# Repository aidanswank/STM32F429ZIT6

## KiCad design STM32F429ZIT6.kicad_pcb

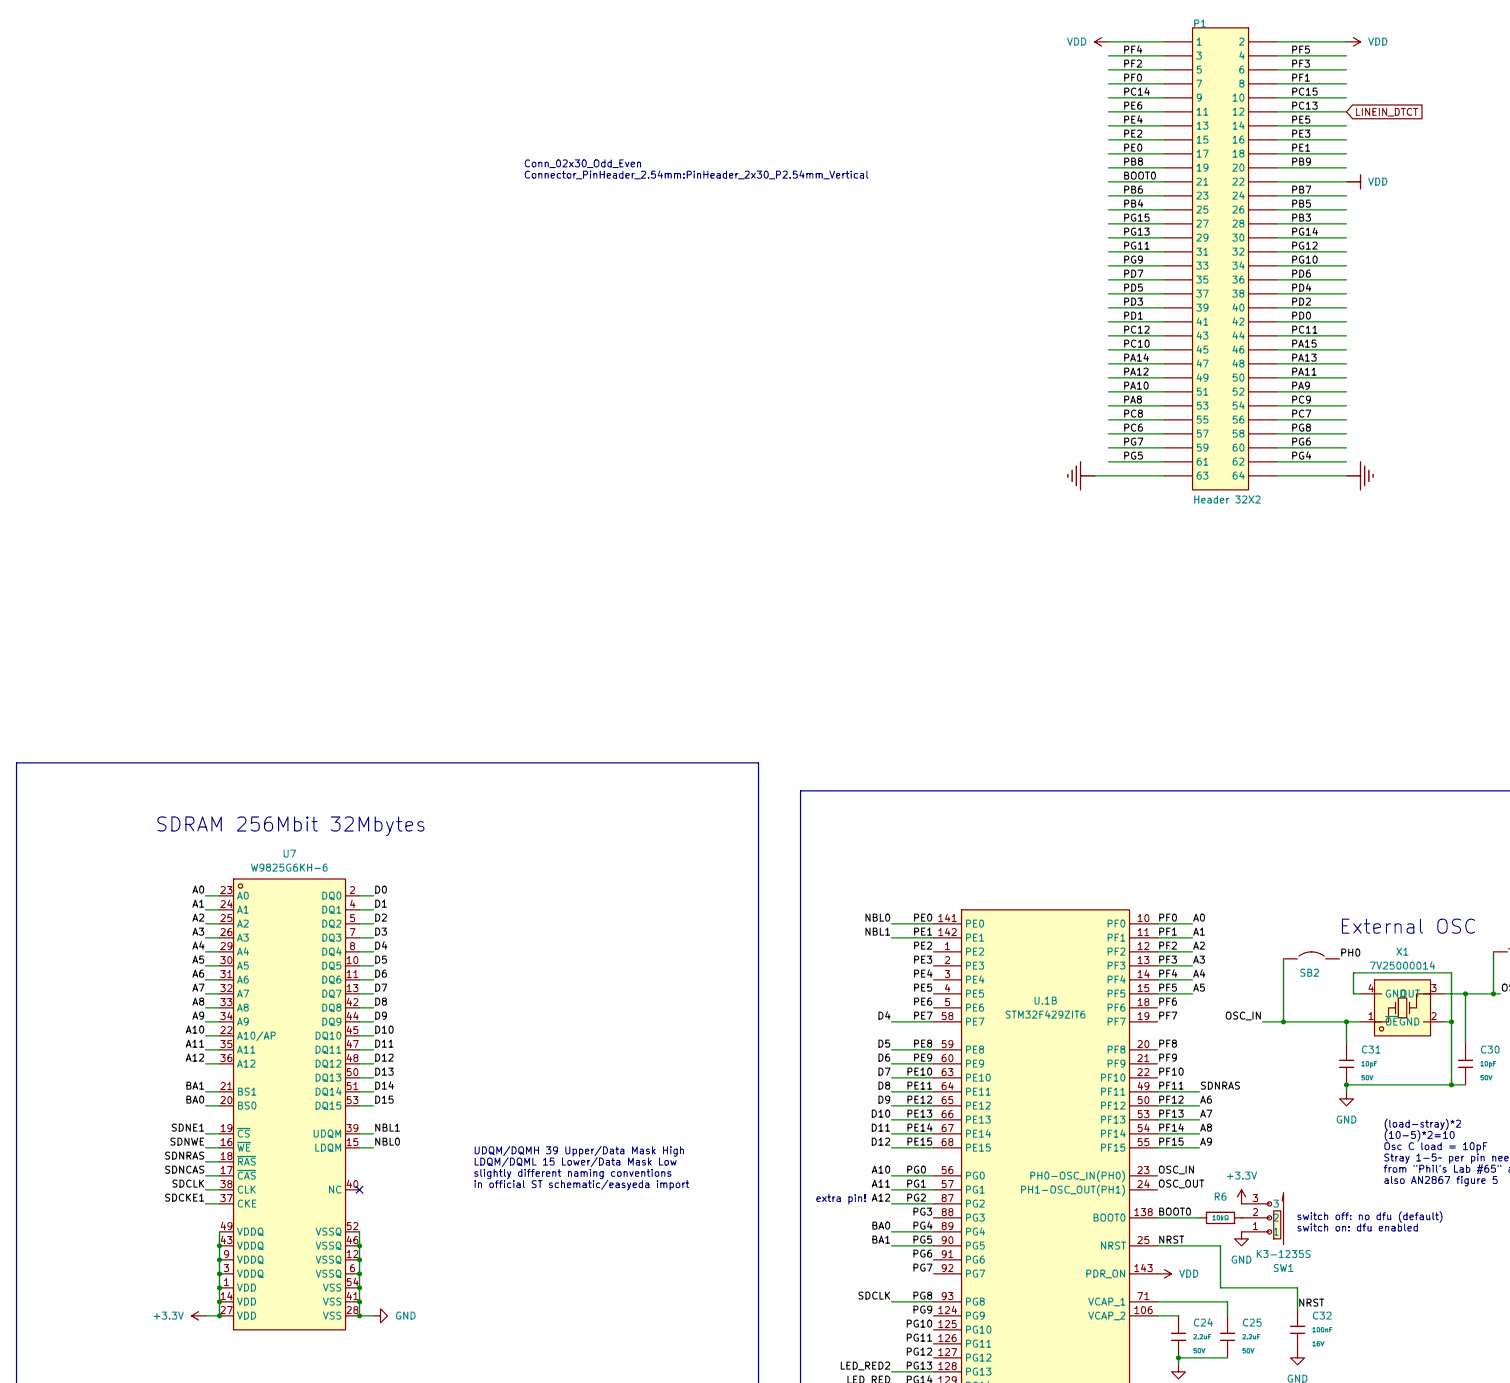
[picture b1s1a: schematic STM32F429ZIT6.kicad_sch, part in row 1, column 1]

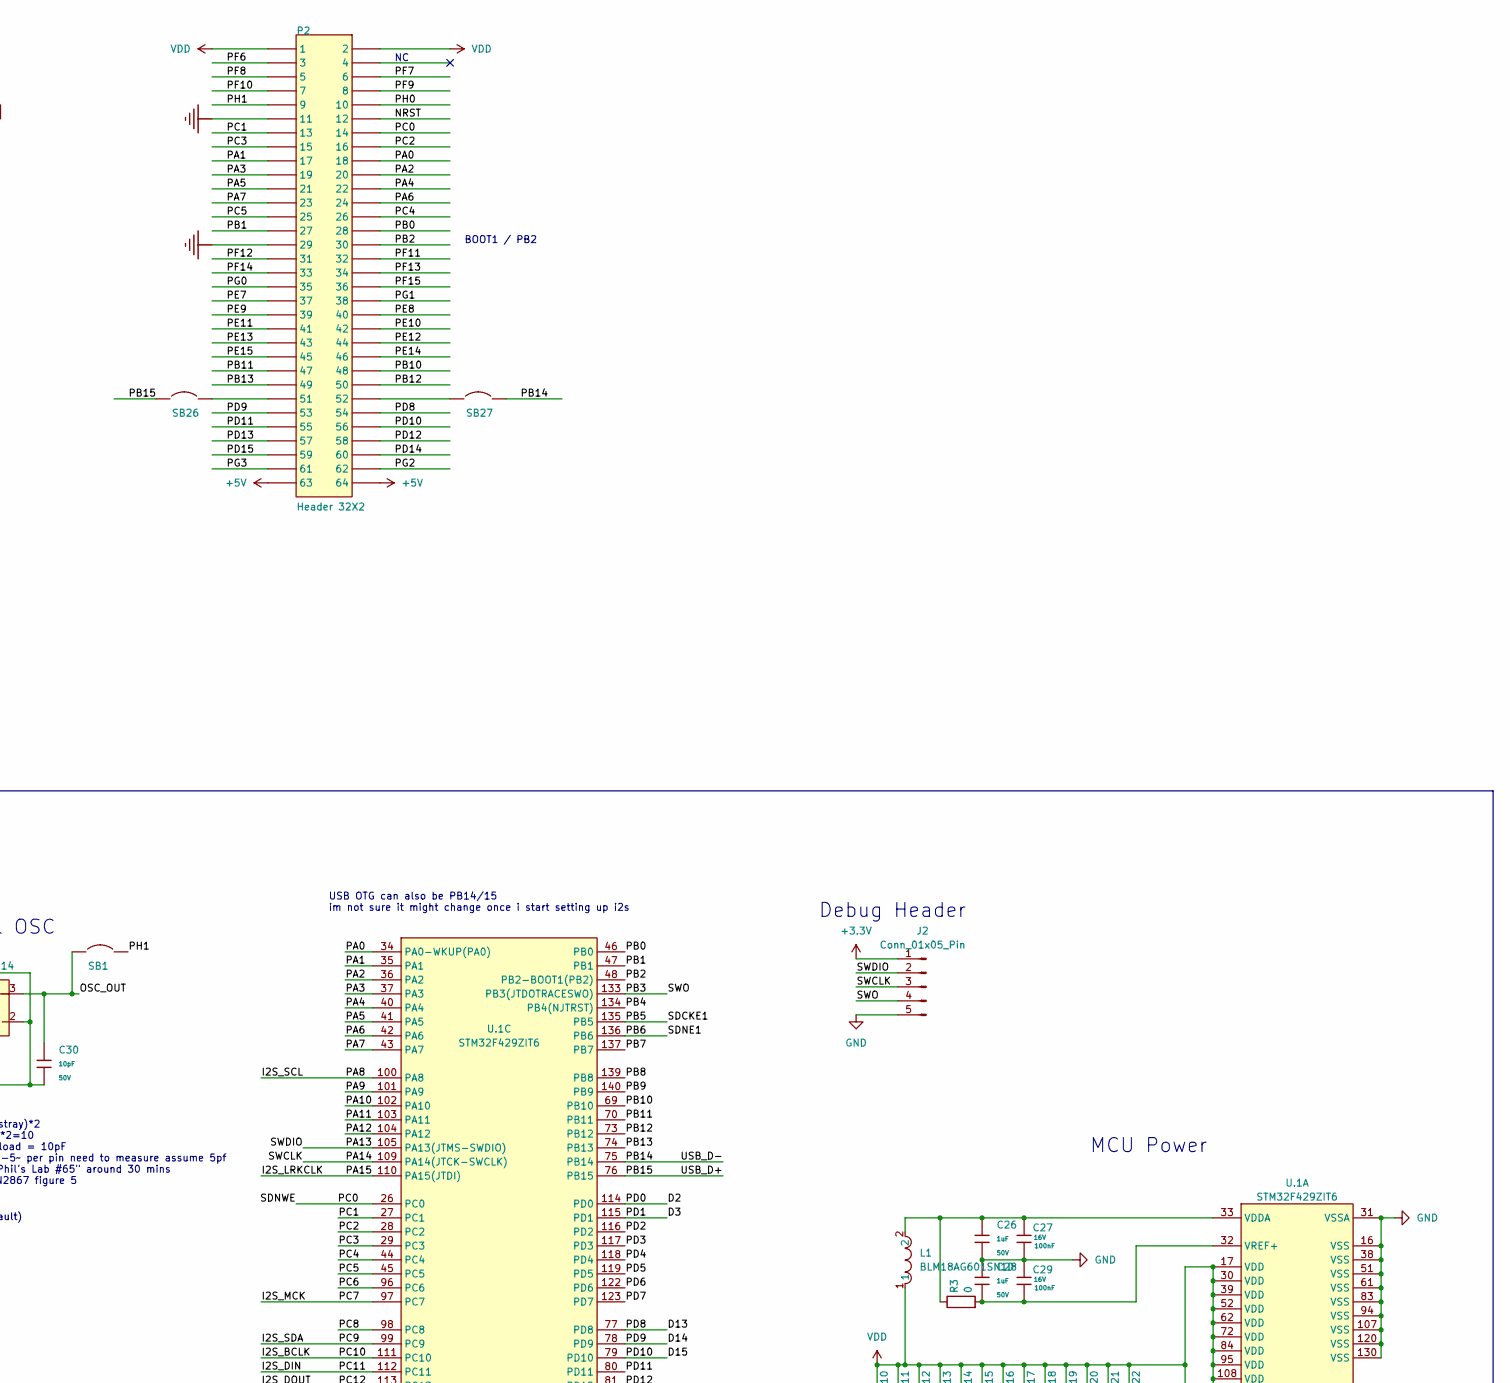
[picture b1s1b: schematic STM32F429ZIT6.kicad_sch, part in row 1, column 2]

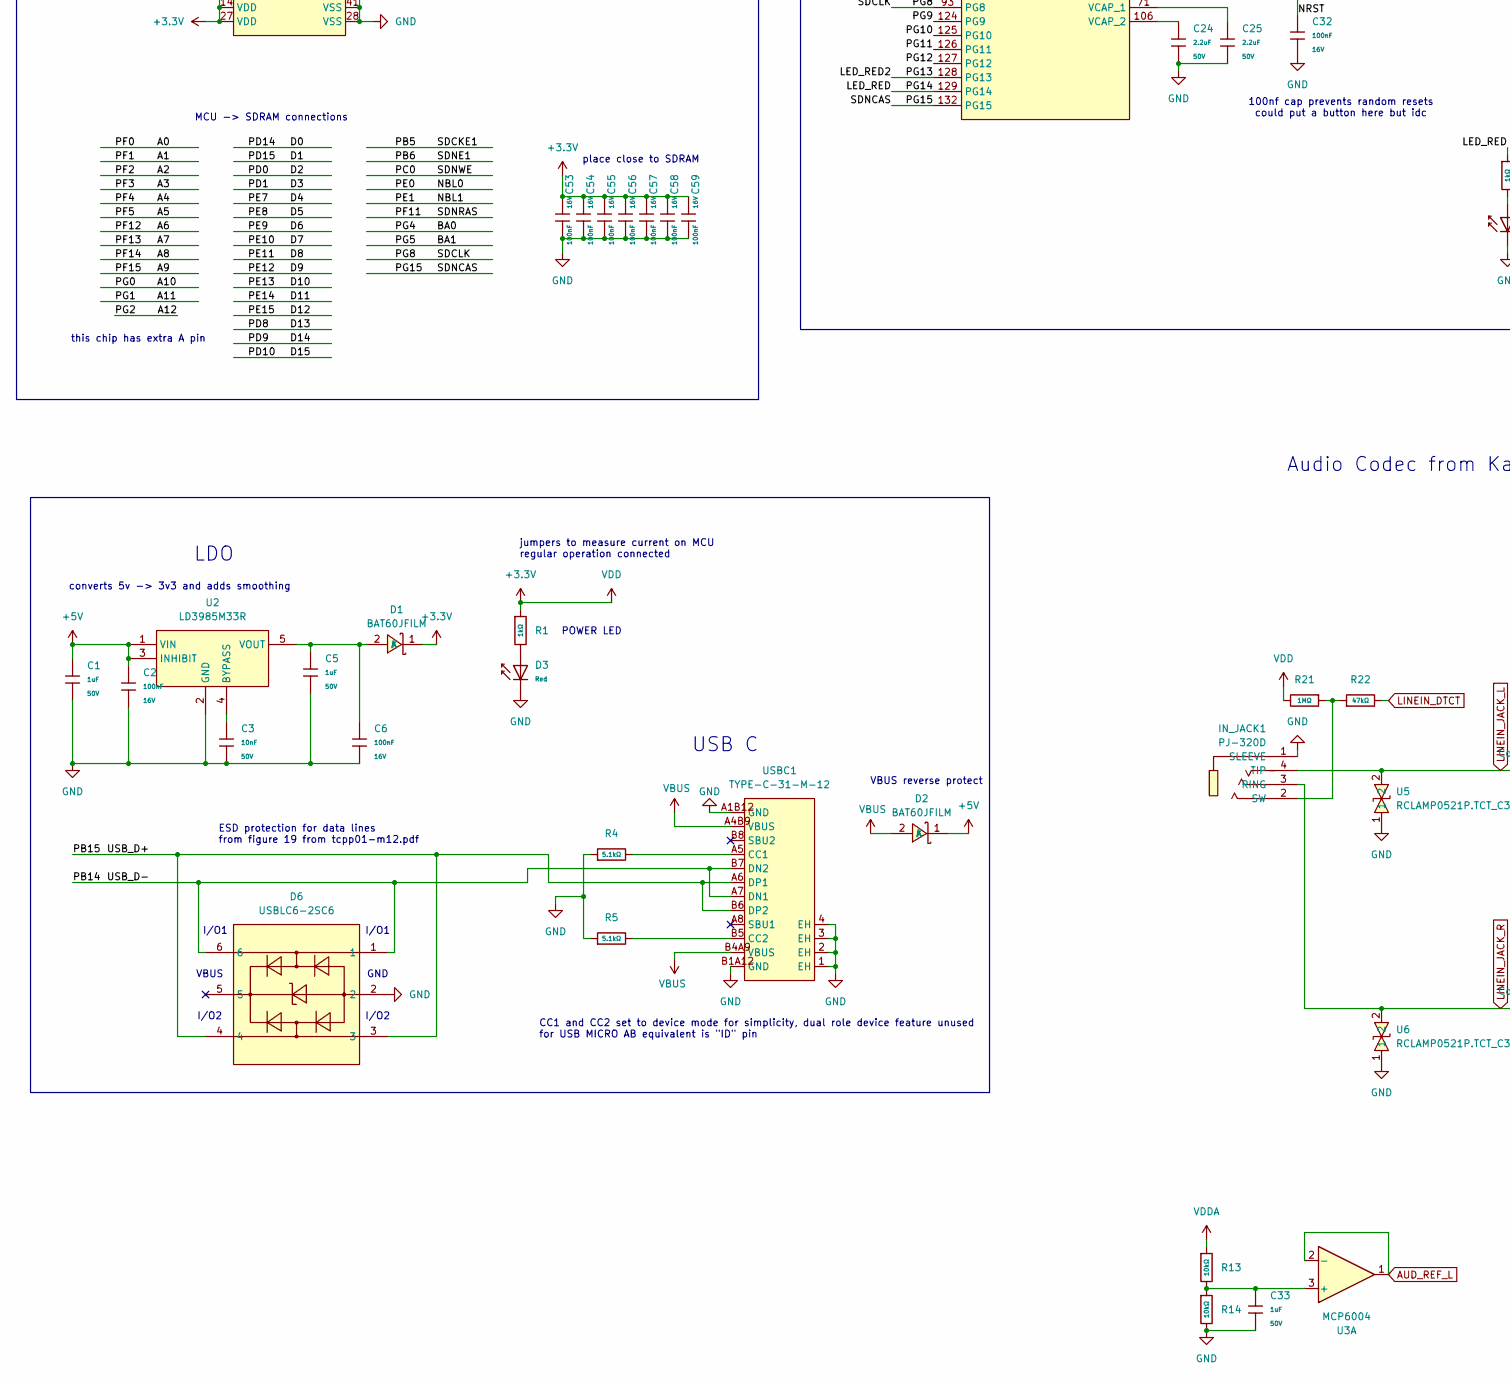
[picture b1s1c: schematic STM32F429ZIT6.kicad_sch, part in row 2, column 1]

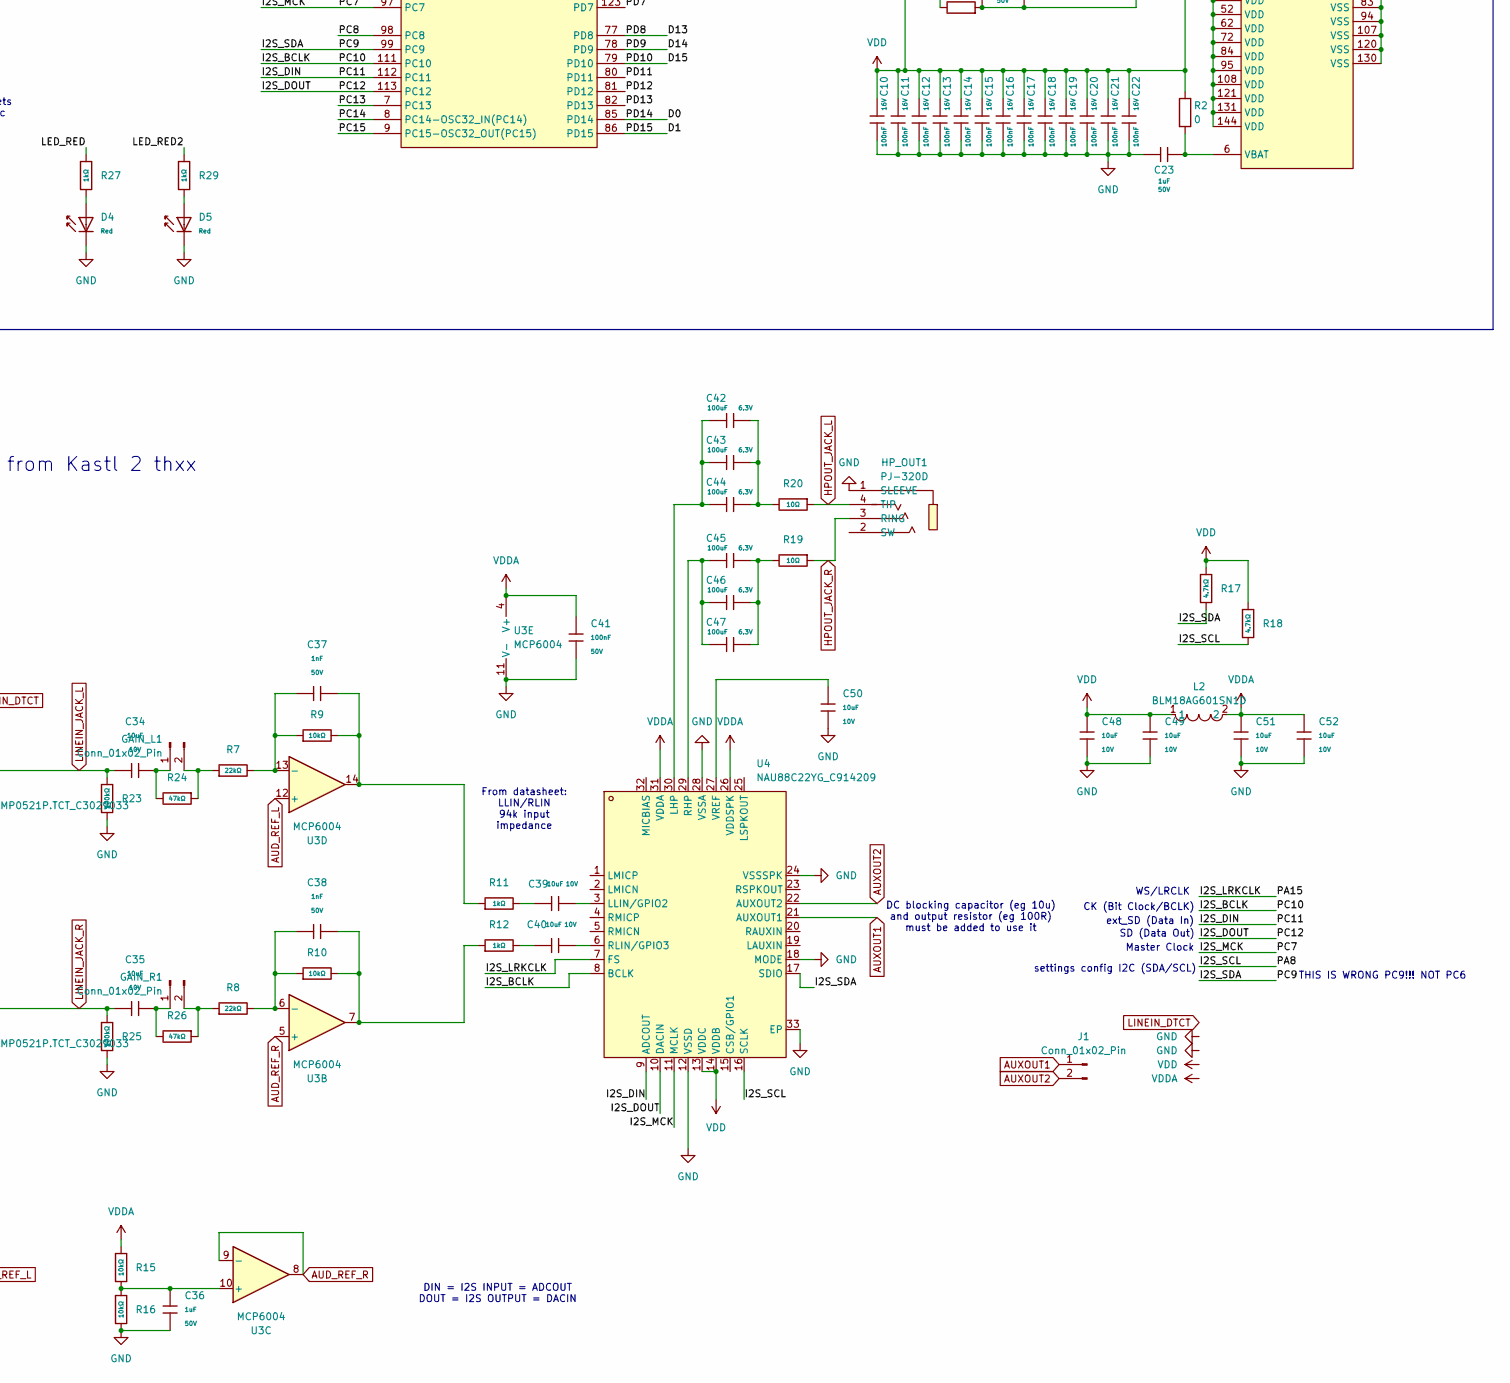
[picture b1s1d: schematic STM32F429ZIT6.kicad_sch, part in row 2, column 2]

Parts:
C1, C5, C23, C33, C36: 1uF; C_0603; Voltage Rated 50V; Tolerance ±10%; Part CL10A105KB8NNNC; LCSC C15849
C2, C6, C10, C11, C12, C13, C14, C15, C16, C17, C18, C19, C20, C21, C22, C27, C29, C32, C53, C54, C55, C56, C57, C58, C59: 100nF; C_0402; Voltage Rated 16V; Tolerance ±10%; Part CL05B104KO5NNNC; LCSC C1525
C3: 10nF; C_0603; Voltage Rated 50V; Tolerance ±10%; Part 0603B103K500NT; LCSC C57112
C24, C25: 2.2uF; C_1206; Voltage Rated 50V; Tolerance ±10%; Part CL31B225KBHNNNE; LCSC C50254
C26, C28: 1uF; C_1206; Voltage Rated 50V; Tolerance ±10%; Part CL31B105KBHNNNE; LCSC C1848
C30, C31: 10pF; C_0402; Voltage Rated 50V; Tolerance ±5%; Part CL05C100JB5NNNC; LCSC C32949
C34, C35, C39, C40, C48, C49, C50, C51, C52: 10uF; C_0603; Voltage Rated 10V; Tolerance ±10%; Part CL10A106KP8NNNC; LCSC C19702
C37, C38: 1nF; C_0603; Voltage Rated 50V; Tolerance ±10%; Part CL10B102KB8NNNC; LCSC C1588
C41: 100nF; C_0603; Voltage Rated 50V; Tolerance ±10%; Part CC0603KRX7R9BB104; LCSC C14663
C42, C43, C44, C45, C46, C47: 100uF; C_1206; Voltage Rated 6.3V; Tolerance ±20%; Part CL31A107MQHNNNE; LCSC C15008
D1, D2: BAT60JFILM; SOD-323_L1.8-W1.3-LS2.5-RD; LCSC Part C133103
D3, D4, D5: Red; D_0603; Part KT-0603R; LCSC C2286
D6: USBLC6-2SC6; SOT-23-6_L2.9-W1.6-P0.95-LS2.8-BL; LCSC Part C7519
GAIN_L1: Conn_01x02_Pin; PinHeader_1x02_P2.54mm_Vertical
GAIN_R1: Conn_01x02_Pin; PinHeader_1x02_P2.54mm_Vertical
HP_OUT1: PJ-320D; AUDIO-SMD_PJ-320D-1; LCSC Part C431535
IN_JACK1: PJ-320D; AUDIO-SMD_PJ-320D-1; LCSC Part C431535
J1: Conn_01x02_Pin; PinHeader_1x02_P2.54mm_Vertical
J2: Conn_01x05_Pin; PinHeader_1x05_P2.54mm_Vertical
L1, L2: BLM18AG601SN1D; L0603; LCSC Part C19330
P1, P2: Header 32X2; PinHeader_2x32_P2.54mm_Vertical
R1, R27, R29: 1kΩ; R_0402; Overload Voltage (Max) 50V; Tolerance ±1%; Part 0402WGF1001TCE; LCSC C11702
R2, R3: 0; R_0402
R4, R5: 5.1kΩ; R_0402; Overload Voltage (Max) 50V; Tolerance ±1%; Part 0402WGF5101TCE; LCSC C25905
R6: 10kΩ; R_0402; Overload Voltage (Max) 50V; Tolerance ±1%; Part 0402WGF1002TCE; LCSC C25744
R7, R8: 22kΩ; R_0603; Overload Voltage (Max) 75V; Tolerance ±1%; Part 0603WAF2202T5E; LCSC C31850
R9, R10, R13, R14, R15, R16: 10kΩ; R_0603; Overload Voltage (Max) 75V; Tolerance ±1%; Part 0603WAF1002T5E; LCSC C25804
R11, R12: 1kΩ; R_0603; Overload Voltage (Max) 75V; Tolerance ±1%; Part 0603WAF1001T5E; LCSC C21190
R17, R18: 4.7kΩ; R_0603; Overload Voltage (Max) 75V; Tolerance ±1%; Part 0603WAF4701T5E; LCSC C23162
R19, R20: 10Ω; R_0805; Overload Voltage (Max) 150V; Tolerance ±1%; Part 0805W8F100JT5E; LCSC C17415
R21: 1MΩ; R_0603; Overload Voltage (Max) 75V; Tolerance ±1%; Part 0603WAF1004T5E; LCSC C22935
R22, R24, R26: 47kΩ; R_0603; Overload Voltage (Max) 75V; Tolerance ±1%; Part 0603WAF4702T5E; LCSC C25819
R23, R25: 100kΩ; R_0603; Overload Voltage (Max) 75V; Tolerance ±1%; Part 0603WAF1003T5E; LCSC C25803
SB1, SB2, SB26, SB27: Circuit Breaker; SolderJumper-2_P1.3mm_Open_TrianglePad1.0x1.5mm
SW1: K3-1235S; SW-SMD_K3-1235S-K1; LCSC Part C92660
U2: LD3985M33R; SOT-23-5_L3.0-W1.7-P0.95-LS2.8-BR; LCSC Part C46243
U3: MCP6004; SOIC-14_L8.7-W3.9-P1.27-LS6.0-BL; LCSC Part C7378
U4: NAU88C22YG_C914209; QFN-32_L5.0-W5.0-P0.50-BL-EP2.7; LCSC Part C914209
U5, U6: RCLAMP0521P.TCT_C3029033; D0402-BI; LCSC Part C3029033
U7: W9825G6KH-6; TSOP-54_L22.2-W10.2-P0.80-LS11.8-BL; LCSC Part C62246
U.1: STM32F429ZIT6; LQFP-144_L20.0-W20.0-P0.50-LS22.0-BL; LCSC Part C84808
USBC1: TYPE-C-31-M-12; USB-C_SMD-TYPE-C-31-M-12_1; LCSC Part C165948
X1: 7V25000014; CRYSTAL-SMD_4P-L3.2-W2.5-BL-1; LCSC Part C337206

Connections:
+3.3V: C10.1, C11.1, C12.1, C13.1, C14.1, C15.1, C16.1, C17.1, C18.1, C19.1, C20.1, C21.1, C22.1, C48.1, C49.1, C53.1, C54.1, C55.1, C56.1, C57.1, C58.1, C59.1, D1.1 (K), J2.1, L1.1, L2.1, P1.1, P1.2, P1.22, P2.1, P2.2, R1.1, R2.1, R17.1, R18.1, R21.2, SW1.3, U4.13 (VDDC), U4.14 (VDDB), U7.1 (VDD), U7.3 (VDDQ), U7.9 (VDDQ), U7.14 (VDD), U7.27 (VDD), U7.43 (VDDQ), U7.49 (VDDQ), U.1.17 (VDD), U.1.30 (VDD), U.1.39 (VDD), U.1.52 (VDD), U.1.62 (VDD), U.1.72 (VDD), U.1.84 (VDD), U.1.95 (VDD), U.1.108 (VDD), U.1.121 (VDD), U.1.131 (VDD), U.1.143 (PDR_ON), U.1.144 (VDD)
+5V: C1.1, C2.1, D2.1 (K), P2.63, P2.64, U2.1 (VIN), U2.3 (INHIBIT)
/A0: P1.7, U7.23 (A0), U.1.10 (PF0)
/A1: P1.8, U7.24 (A1), U.1.11 (PF1)
/A2: P1.5, U7.25 (A2), U.1.12 (PF2)
/A3: P1.6, U7.26 (A3), U.1.13 (PF3)
/A4: P1.3, U7.29 (A4), U.1.14 (PF4)
/A5: P1.4, U7.30 (A5), U.1.15 (PF5)
/A6: P2.31, U7.31 (A6), U.1.50 (PF12)
/A7: P2.34, U7.32 (A7), U.1.53 (PF13)
/A8: P2.33, U7.33 (A8), U.1.54 (PF14)
/A9: P2.36, U7.34 (A9), U.1.55 (PF15)
/A10: P2.35, U7.22 (A10/AP), U.1.56 (PG0)
/A11: P2.38, U7.35 (A11), U.1.57 (PG1)
/A12: P2.62, U7.36 (A12), U.1.87 (PG2)
/BA0: P1.62, U7.20 (BS0), U.1.89 (PG4)
/BA1: P1.61, U7.21 (BS1), U.1.90 (PG5)
/BOOT0: P1.21, R6.2, U.1.138 (BOOT0)
/D0: P2.60, U7.2 (DQ0), U.1.85 (PD14)
/D1: P2.59, U7.4 (DQ1), U.1.86 (PD15)
/D2: P1.42, U7.5 (DQ2), U.1.114 (PD0)
/D3: P1.41, U7.7 (DQ3), U.1.115 (PD1)
/D4: P2.37, U7.8 (DQ4), U.1.58 (PE7)
/D5: P2.40, U7.10 (DQ5), U.1.59 (PE8)
/D6: P2.39, U7.11 (DQ6), U.1.60 (PE9)
/D7: P2.42, U7.13 (DQ7), U.1.63 (PE10)
/D8: P2.41, U7.42 (DQ8), U.1.64 (PE11)
/D9: P2.44, U7.44 (DQ9), U.1.65 (PE12)
/D10: P2.43, U7.45 (DQ10), U.1.66 (PE13)
/D11: P2.46, U7.47 (DQ11), U.1.67 (PE14)
/D12: P2.45, U7.48 (DQ12), U.1.68 (PE15)
/D13: P2.54, U7.50 (DQ13), U.1.77 (PD8)
/D14: P2.53, U7.51 (DQ14), U.1.78 (PD9)
/D15: P2.56, U7.53 (DQ15), U.1.79 (PD10)
/I2S_BCLK: P1.45, U4.8 (BCLK), U.1.111 (PC10)
/I2S_DIN: P1.44, U4.9 (ADCOUT), U.1.112 (PC11)
/I2S_DOUT: P1.43, U4.10 (DACIN), U.1.113 (PC12)
/I2S_LRKCLK: P1.46, U4.7 (FS), U.1.110 (PA15(JTDI))
/I2S_MCK: P1.56, U4.11 (MCLK), U.1.97 (PC7)
/I2S_SCL: P1.53, R18.2, U4.16 (SCLK), U.1.100 (PA8)
/I2S_SDA: P1.54, R17.2, U4.17 (SDIO), U.1.99 (PC9)
/LED_RED: P1.30, R27.1, U.1.129 (PG14)
/LED_RED2: P1.29, R29.1, U.1.128 (PG13)
/NBL0: P1.17, U7.15 (LDQM), U.1.141 (PE0)
/NBL1: P1.18, U7.39 (UDQM), U.1.142 (PE1)
/NRST: C32.1, P2.12, U.1.25 (NRST)
/OSC_IN: C31.1, SB2.1, U.1.23 (PH0-OSC_IN(PH0)), X1.1 (~OE)
/OSC_OUT: C30.1, SB1.1, U.1.24 (PH1-OSC_OUT(PH1)), X1.3 (OUT)
/PA0: P2.18, U.1.34 (PA0-WKUP(PA0))
/PA1: P2.17, U.1.35 (PA1)
/PA2: P2.20, U.1.36 (PA2)
/PA3: P2.19, U.1.37 (PA3)
/PA4: P2.22, U.1.40 (PA4)
/PA5: P2.21, U.1.41 (PA5)
/PA6: P2.24, U.1.42 (PA6)
/PA7: P2.23, U.1.43 (PA7)
/PA9: P1.52, U.1.101 (PA9)
/PA10: P1.51, U.1.102 (PA10)
/PA11: P1.50, U.1.103 (PA11)
/PA12: P1.49, U.1.104 (PA12)
/PA13: J2.2, P1.48, U.1.105 (PA13(JTMS-SWDIO))
/PA14: J2.3, P1.47, U.1.109 (PA14(JTCK-SWCLK))
/PB0: P2.28, U.1.46 (PB0)
/PB1: P2.27, U.1.47 (PB1)
/PB2: P2.30, U.1.48 (PB2-BOOT1(PB2))
/PB3: J2.4, P1.28, U.1.133 (PB3(JTDOTRACESWO))
/PB4: P1.25, U.1.134 (PB4(NJTRST))
/PB5: P1.26, U7.37 (CKE), U.1.135 (PB5)
/PB6: P1.23, U7.19 (~CS), U.1.136 (PB6)
/PB7: P1.24, U.1.137 (PB7)
/PB8: P1.19, U.1.139 (PB8)
/PB9: P1.20, U.1.140 (PB9)
/PB10: P2.48, U.1.69 (PB10)
/PB11: P2.47, U.1.70 (PB11)
/PB12: P2.50, U.1.73 (PB12)
/PB13: P2.49, U.1.74 (PB13)
/PB14: D6.1, D6.6, SB27.2, U.1.75 (PB14), USBC1.A7 (DN1), USBC1.B7 (DN2)
/PB15: D6.3, D6.4, SB26.1, U.1.76 (PB15), USBC1.A6 (DP1), USBC1.B6 (DP2)
/PC0: P2.14, U7.16 (~WE), U.1.26 (PC0)
/PC1: P2.13, U.1.27 (PC1)
/PC2: P2.16, U.1.28 (PC2)
/PC3: P2.15, U.1.29 (PC3)
/PC4: P2.26, U.1.44 (PC4)
/PC5: P2.25, U.1.45 (PC5)
/PC6: P1.57, U.1.96 (PC6)
/PC8: P1.55, U.1.98 (PC8)
/PC14: P1.9, U.1.8 (PC14-OSC32_IN(PC14))
/PC15: P1.10, U.1.9 (PC15-OSC32_OUT(PC15))
/PD2: P1.40, U.1.116 (PD2)
/PD3: P1.39, U.1.117 (PD3)
/PD4: P1.38, U.1.118 (PD4)
/PD5: P1.37, U.1.119 (PD5)
/PD6: P1.36, U.1.122 (PD6)
/PD7: P1.35, U.1.123 (PD7)
/PD11: P2.55, U.1.80 (PD11)
/PD12: P2.58, U.1.81 (PD12)
/PD13: P2.57, U.1.82 (PD13)
/PE2: P1.15, U.1.1 (PE2)
/PE3: P1.16, U.1.2 (PE3)
/PE4: P1.13, U.1.3 (PE4)
/PE5: P1.14, U.1.4 (PE5)
/PE6: P1.11, U.1.5 (PE6)
/PF6: P2.3, U.1.18 (PF6)
/PF7: P2.6, U.1.19 (PF7)
/PF8: P2.5, U.1.20 (PF8)
/PF9: P2.8, U.1.21 (PF9)
/PF10: P2.7, U.1.22 (PF10)
/PF11: P2.32, U7.18 (~RAS), U.1.49 (PF11)
/PG3: P2.61, U.1.88 (PG3)
/PG6: P1.60, U.1.91 (PG6)
/PG7: P1.59, U.1.92 (PG7)
/PG8: P1.58, U7.38 (CLK), U.1.93 (PG8)
/PG9: P1.33, U.1.124 (PG9)
/PG10: P1.34, U.1.125 (PG10)
/PG11: P1.31, U.1.126 (PG11)
/PG12: P1.32, U.1.127 (PG12)
/PG15: P1.27, U7.17 (~CAS), U.1.132 (PG15)
/PH0: P2.10, SB2.2
/PH1: P2.9, SB1.2
AUD_REF_L: U3.1, U3.2 (-), U3.12 (+)
AUD_REF_R: U3.5 (+), U3.8, U3.9 (-)
AUXOUT1: J1.1, U4.21 (AUXOUT1)
AUXOUT2: J1.2, U4.22 (AUXOUT2)
GND: C1.2, C2.2, C3.2, C5.2, C6.2, C10.2, C11.2, C12.2, C13.2, C14.2, C15.2, C16.2, C17.2, C18.2, C19.2, C20.2, C21.2, C22.2, C23.1, C24.2, C25.2, C26.2, C27.2, C28.1, C29.1, C30.2, C31.2, C32.2, C33.2, C36.2, C41.2, C48.2, C49.2, C50.2, C51.2, C52.2, C53.2, C54.2, C55.2, C56.2, C57.2, C58.2, C59.2, D3.1, D4.1, D5.1, D6.2, HP_OUT1.1 (SLEEVE), IN_JACK1.1 (SLEEVE), J2.5, P1.63, P1.64, P2.11, P2.29, R4.1, R5.1, R14.2, R16.2, R23.2, R25.2, SW1.1, U2.2 (GND), U3.11 (V-), U4.12 (VSSD), U4.18 (MODE), U4.24 (VSSSPK), U4.28 (VSSA), U4.33 (EP), U5.1, U6.1, U7.6 (VSSQ), U7.12 (VSSQ), U7.28 (VSS), U7.41 (VSS), U7.46 (VSSQ), U7.52 (VSSQ), U7.54 (VSS), U.1.16 (VSS), U.1.31 (VSSA), U.1.38 (VSS), U.1.51 (VSS), U.1.61 (VSS), U.1.83 (VSS), U.1.94 (VSS), U.1.107 (VSS), U.1.120 (VSS), U.1.130 (VSS), USBC1.1 (EH), USBC1.2 (EH), USBC1.3 (EH), USBC1.4 (EH), USBC1.A1B12 (GND), USBC1.B1A12 (GND), X1.2 (GND), X1.4 (GND)
HPOUT_JACK_L: HP_OUT1.4 (TIP), R20.1
HPOUT_JACK_R: HP_OUT1.3 (RING), R19.1
LINEIN_DTCT: P1.12, R22.2, U.1.7 (PC13)
LINEIN_JACK_L: C34.1, IN_JACK1.4 (TIP), R23.1, U5.2
LINEIN_JACK_R: C35.1, IN_JACK1.3 (RING), R25.1, U6.2
unnamed: C37.2, R9.2, R11.1, U3.14
unnamed: C38.2, R10.2, R12.1, U3.7
unnamed: C39.1, R11.2
unnamed: C40.1, R12.2
unnamed: C42.2, C43.2, C44.2, R20.2
unnamed: C45.2, C46.2, C47.2, R19.2
unnamed: C5.1, C6.1, D1.2 (A), U2.5 (VOUT)
unnamed: D3.2, R1.2
unnamed: D4.2, R27.2
unnamed: D5.2, R29.2
unnamed: C34.2, GAIN_L1.1, R24.2
unnamed: GAIN_L1.2, R7.1, R24.1
unnamed: C35.2, GAIN_R1.1, R26.2
unnamed: GAIN_R1.2, R8.1, R26.1
unnamed: IN_JACK1.2 (SW), R21.1, R22.1
unnamed: P2.51, SB26.2
unnamed: P2.52, SB27.1
unnamed: R6.1, SW1.2
unnamed: C3.1, U2.4 (BYPASS)
unnamed: C33.1, R13.2, R14.1, U3.3 (+)
unnamed: C38.1, R8.2, R10.1, U3.6 (-)
unnamed: C36.1, R15.2, R16.1, U3.10 (+)
unnamed: C37.1, R7.2, R9.1, U3.13 (-)
unnamed: C42.1, C43.1, C44.1, U4.30 (LHP)
unnamed: C39.2, U4.3 (LLIN/GPIO2)
unnamed: C45.1, C46.1, C47.1, U4.29 (RHP)
unnamed: C40.2, U4.6 (RLIN/GPIO3)
unnamed: C50.1, U4.27 (VREF)
unnamed: C23.2, R2.2, U.1.6 (VBAT)
unnamed: C26.1, C27.1, L1.2, R3.1, U.1.33 (VDDA)
unnamed: C28.2, C29.2, R3.2, U.1.32 (VREF+)
unnamed: C25.1, U.1.71 (VCAP_1)
unnamed: C24.1, U.1.106 (VCAP_2)
unnamed: R4.2, USBC1.A5 (CC1)
unnamed: R5.2, USBC1.B5 (CC2)
VBUS: D2.2 (A), USBC1.A4B9 (VBUS), USBC1.B4A9 (VBUS)
VDDA: C41.1, C51.1, C52.1, L2.2, R13.1, R15.1, U3.4 (V+), U4.26 (VDDSPK), U4.31 (VDDA)

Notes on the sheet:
DIN = I2S INPUT = ADCOUT DOUT = I2S OUTPUT = DACIN
converts 5v -> 3v3 and adds smoothing
ext_SD (Data In)
THIS IS WRONG PC9!!! NOT PC6
UDQM/DQMH 39 Upper/Data Mask High LDQM/DQML 15 Lower/Data Mask Low slightly different naming conventions in official ST schematic/easyeda import
Conn_02x30_Odd_Even Connector_PinHeader_2.54mm:PinHeader_2x30_P2.54mm_Vertical
(load-stray)*2 (10-5)*2=10 Osc C load = 10pF Stray 1-5~ per pin need to measure assume 5pf from "Phil's Lab #65" around 30 mins also AN2867 figure 5
MCU Power
ESD protection for data lines from figure 19 from tcpp01-m12.pdf
place close to SDRAM
I/O1
LDO
BOOT1 / PB2
VBUS
SD (Data Out)
From datasheet: LLIN/RLIN 94k input impedance
Audio Codec from Kastl 2 thxx
CC1 and CC2 set to device mode for simplicity, dual role device feature unused for USB MICRO AB equivalent is "ID" pin
GND
USB OTG can also be PB14/15 im not sure it might change once i start setting up i2s
SDRAM 256Mbit 32Mbytes
External OSC
POWER LED
DC blocking capacitor (eg 10u) and output resistor (eg 100R) must be added to use it
WS/LRCLK
USB C
CK (Bit Clock/BCLK)
settings config I2C (SDA/SCL)
jumpers to measure current on MCU regular operation connected
this chip has extra A pin
I/O2
VBUS reverse protect
extra pin!
Debug Header
100nf cap prevents random resets could put a button here but idc
Master Clock
switch off: no dfu (default) switch on: dfu enabled
MCU -> SDRAM connections

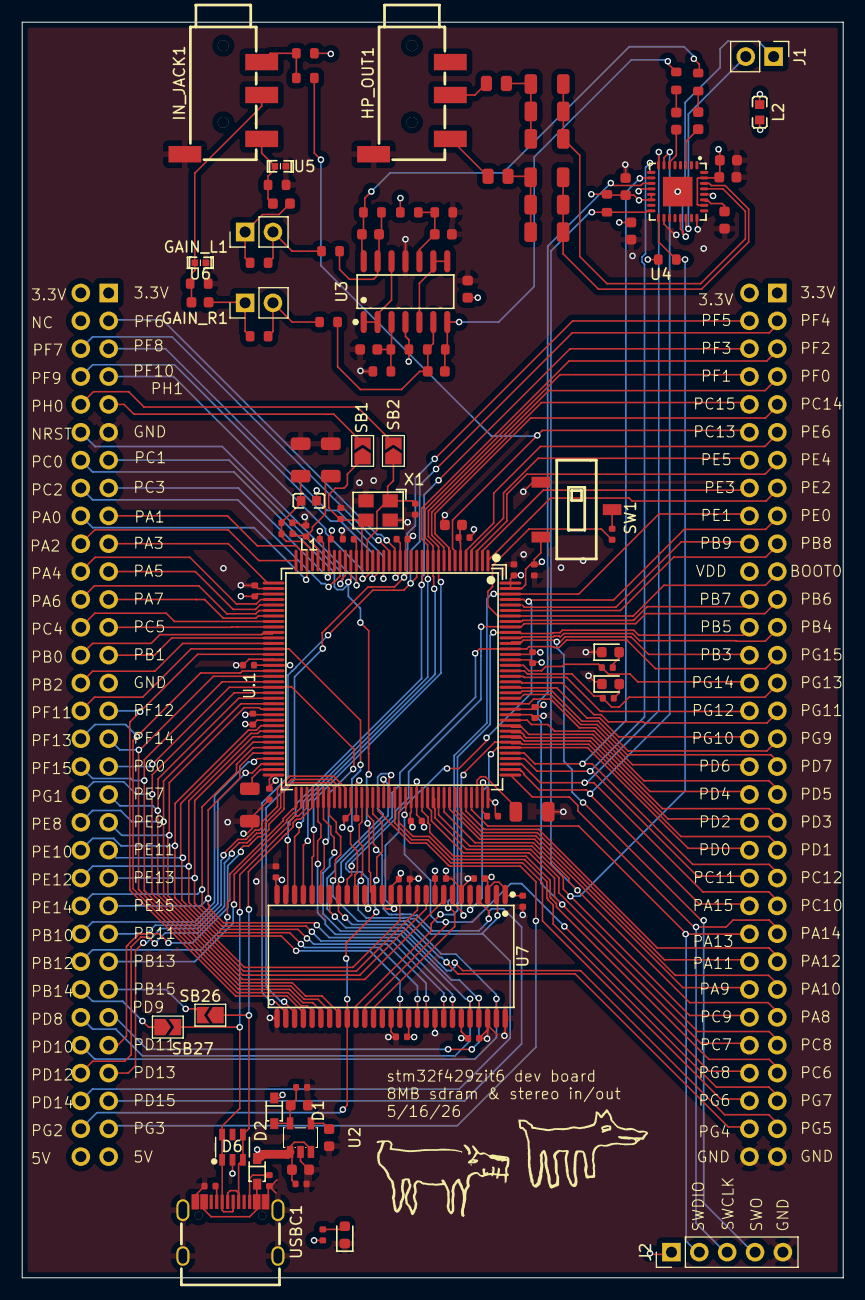
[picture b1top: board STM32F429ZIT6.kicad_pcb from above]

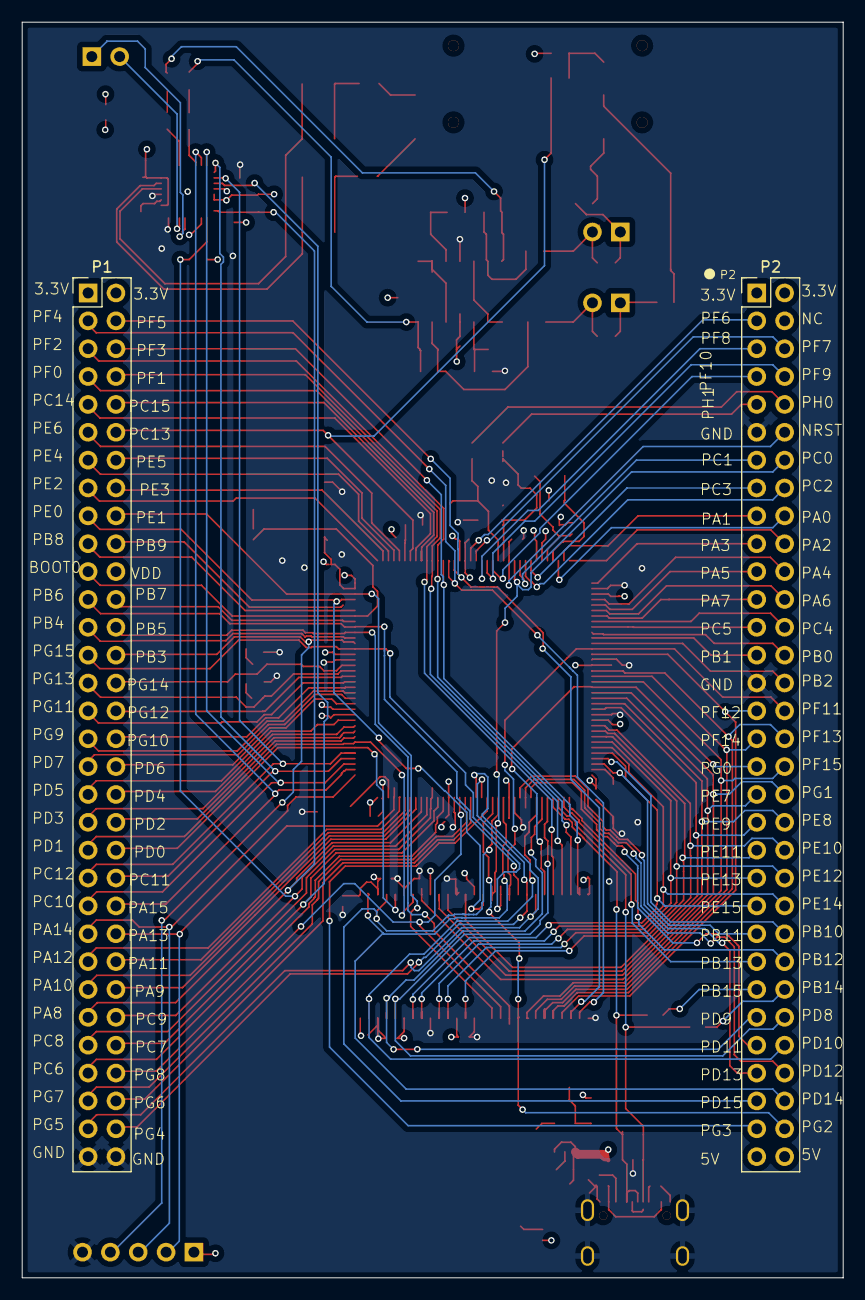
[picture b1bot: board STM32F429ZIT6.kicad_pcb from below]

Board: 4 copper layers, 74.8 x 114.5 mm, 113 parts (2 on the bottom side), 166 nets.

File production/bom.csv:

Designator,Footprint,Quantity,Value,LCSC Part #
"C1, C23, C33, C36, C5",C_0603,5,1uF,C15849
"C10, C11, C12, C13, C14, C15, C16, C17, C18, C19, C2, C20, C21, C22, C27, C29, C32, C53, C54, C55, C56, C57, C58, C59, C6",C_0402,25,100nF,C1525
"C24, C25",C_1206,2,2.2uF,C50254
"C26, C28",C_1206,2,1uF,C1848
C3,C_0603,1,10nF,C57112
"C30, C31",C_0402,2,10pF,C32949
"C34, C35, C39, C40, C48, C49, C50, C51, C52",C_0603,9,10uF,C19702
"C37, C38",C_0603,2,1nF,C1588
C41,C_0603,1,100nF,C14663
"C42, C43, C44, C45, C46, C47",C_1206,6,100uF,C15008
"D1, D2",SOD-323_L1.8-W1.3-LS2.5-RD,2,BAT60JFILM,C133103
"D3, D4, D5",D_0603,3,Red,C2286
D6,SOT-23-6_L2.9-W1.6-P0.95-LS2.8-BL,1,USBLC6-2SC6,C7519
"GAIN_L1, GAIN_R1, J1",PinHeader_1x02_P2.54mm_Vertical,3,Conn_01x02_Pin,
"HP_OUT1, IN_JACK1",AUDIO-SMD_PJ-320D-1,2,PJ-320D,C431535
J2,PinHeader_1x05_P2.54mm_Vertical,1,Conn_01x05_Pin,
"L1, L2",L0603,2,BLM18AG601SN1D,C19330
"P1, P2",PinHeader_2x32_P2.54mm_Vertical,2,Header 32X2,
"R1, R27, R29",R_0402,3,1kΩ,C11702
"R10, R13, R14, R15, R16, R9",R_0603,6,10kΩ,C25804
"R11, R12",R_0603,2,1kΩ,C21190
"R17, R18",R_0603,2,4.7kΩ,C23162
"R19, R20",R_0805,2,10Ω,C17415
"R2, R3",R_0402,2,0,
R21,R_0603,1,1MΩ,C22935
"R22, R24, R26",R_0603,3,47kΩ,C25819
"R23, R25",R_0603,2,100kΩ,C25803
"R4, R5",R_0402,2,5.1kΩ,C25905
R6,R_0402,1,10kΩ,C25744
"R7, R8",R_0603,2,22kΩ,C31850
"SB1, SB2, SB26, SB27",SolderJumper-2_P1.3mm_Open_TrianglePad1.0x1.5mm,4,Circuit Breaker,
SW1,SW-SMD_K3-1235S-K1,1,K3-1235S,C92660
U.1,LQFP-144_L20.0-W20.0-P0.50-LS22.0-BL,1,STM32F429ZIT6,C84808
U2,SOT-23-5_L3.0-W1.7-P0.95-LS2.8-BR,1,LD3985M33R,C46243
U3,SOIC-14_L8.7-W3.9-P1.27-LS6.0-BL,1,MCP6004,C7378
U4,QFN-32_L5.0-W5.0-P0.50-BL-EP2.7,1,NAU88C22YG_C914209,C914209
"U5, U6",D0402-BI,2,RCLAMP0521P.TCT_C3029033,C3029033
U7,TSOP-54_L22.2-W10.2-P0.80-LS11.8-BL,1,W9825G6KH-6,C62246
USBC1,USB-C_SMD-TYPE-C-31-M-12_1,1,TYPE-C-31-M-12,C165948
X1,CRYSTAL-SMD_4P-L3.2-W2.5-BL-1,1,7V25000014,C337206

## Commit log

2026-05-03 init commit, adding breakout connectors
2026-05-06 quick save
2026-05-07 removing the traces i did on inner layers, gotta keep them clean. moving sd ram to the left to make room
2026-05-07 save before i break everything out instead idk why i didnt do that
2026-05-07 KILL ME!!!!!!!!!!!
2026-05-08 getting closer, one side of the breakout is done ish for the sdram. still needs connections between the sdram and st chip
2026-05-08 didnt save?
2026-05-08 i think sdram is all connected+brokenout
2026-05-08 broke out pb13 12 and 11. they are not used by anything yet
2026-05-08 pg3 breakout also not connected to anything
2026-05-09 closer to breakout done, need to wire codec now
2026-05-09 esd protection for usb data lines
2026-05-14 gpio breakout done?
2026-05-14 no unconnected items i think just some stuff i gotta remove
2026-05-14 18 errors left
2026-05-14 added screen print labels, line in detect need to test
2026-05-14 small edits
2026-05-15 measuring trace lengths, looks ok so far! almost done
2026-05-16 xtal fix
2026-05-16 DONE i think!!!!
2026-05-16 prod zip
